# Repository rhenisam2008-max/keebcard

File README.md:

# KeebCard

A 3-key macropad keychain with an OLED display, built for Hack Club's Stardance event.

## Macropad Design

## Schematic

## PCB Layout

## Case (3D)

## Bill of Materials

| Part | Qty |
|---|---|
| Seeed XIAO RP2040 microcontroller | 1 |
| MX-style mechanical push switches | 3 |
| 0.91" 128×32 I2C OLED display | 1 |

## Firmware
Built with QMK. See `/Firmware` for source.

## Build folders
- `CAD/` — 3D printed case model
- `PCB/` — KiCad schematic and PCB design files
- `Firmware/` — QMK firmware source
- `production/` — Manufacturing-ready files (Gerbers, STEPs, compiled firmware)

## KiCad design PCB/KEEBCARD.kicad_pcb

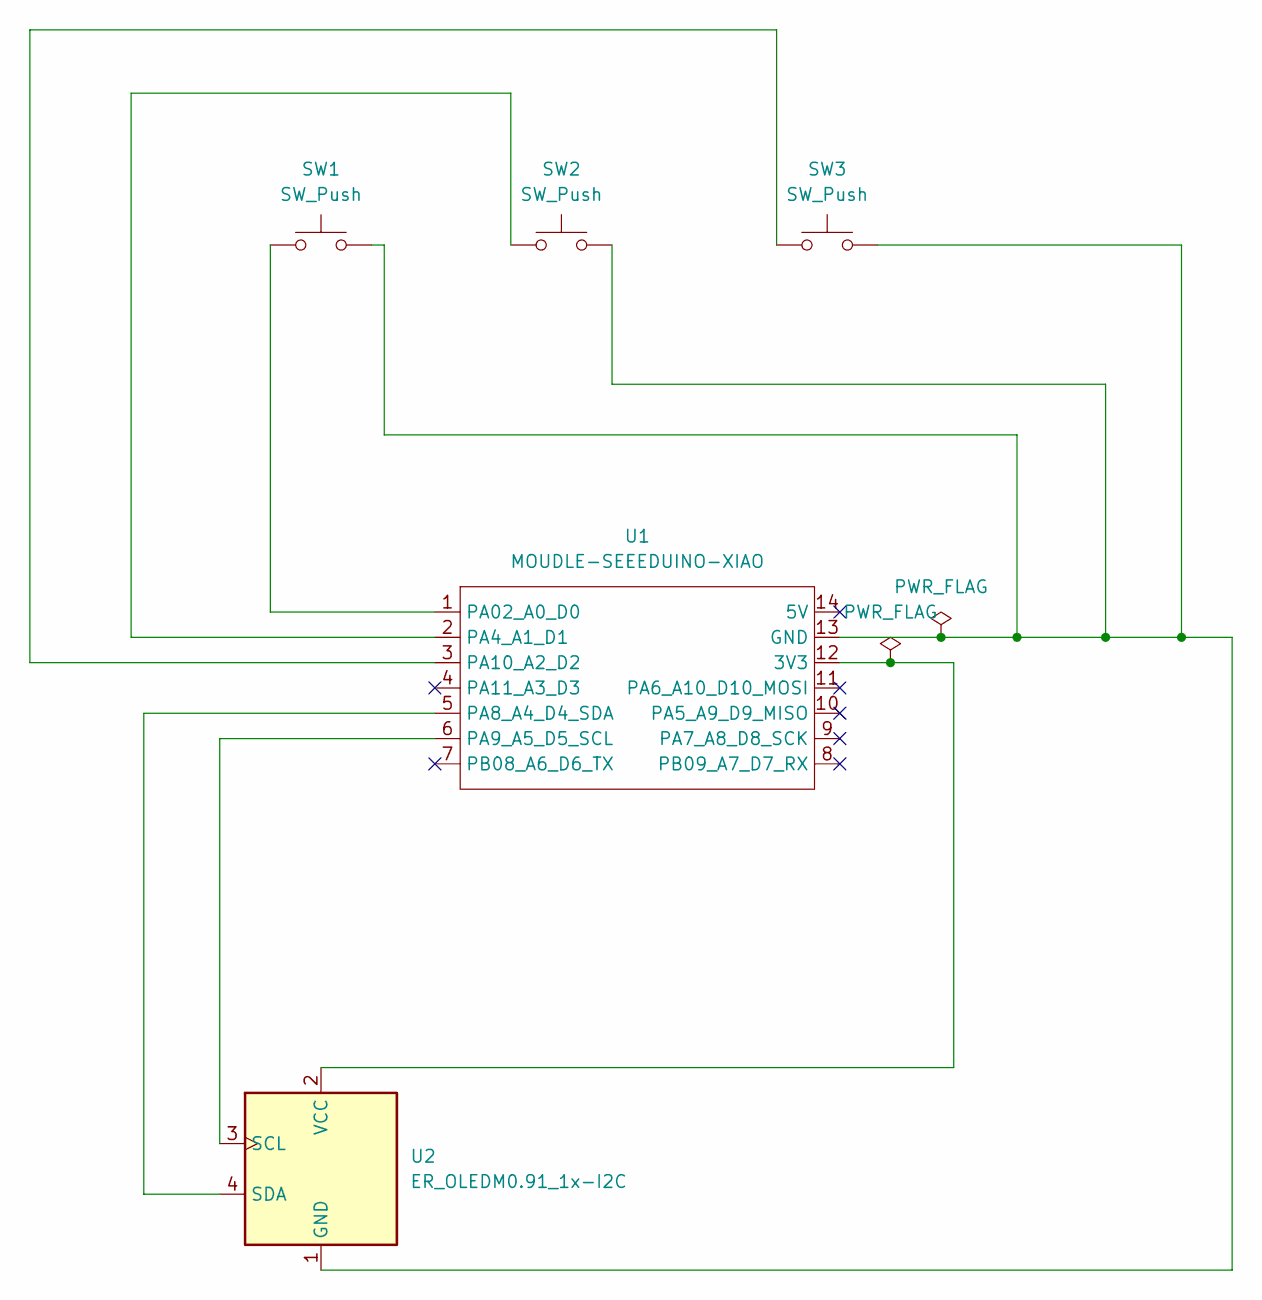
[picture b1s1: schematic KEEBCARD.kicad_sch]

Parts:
SW1, SW2, SW3: SW_Push; SW_Cherry_MX_1.00u_PCB
U1: MOUDLE-SEEEDUINO-XIAO; XIAO-Generic-Hybrid-14P-2.54-21X17.8MM
U2: ER_OLEDM0.91_1x-I2C

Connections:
unnamed: U1.12 (3V3), U2.2 (VCC)
unnamed: SW1.2, SW2.2, SW3.2, U1.13 (GND), U2.1 (GND)
unnamed: SW1.1, U1.1 (PA02_A0_D0)
unnamed: SW2.1, U1.2 (PA4_A1_D1)
unnamed: U1.5 (PA8_A4_D4_SDA), U2.4 (SDA)
unnamed: U1.6 (PA9_A5_D5_SCL), U2.3 (SCL)
unnamed: SW3.1, U1.3 (PA10_A2_D2)

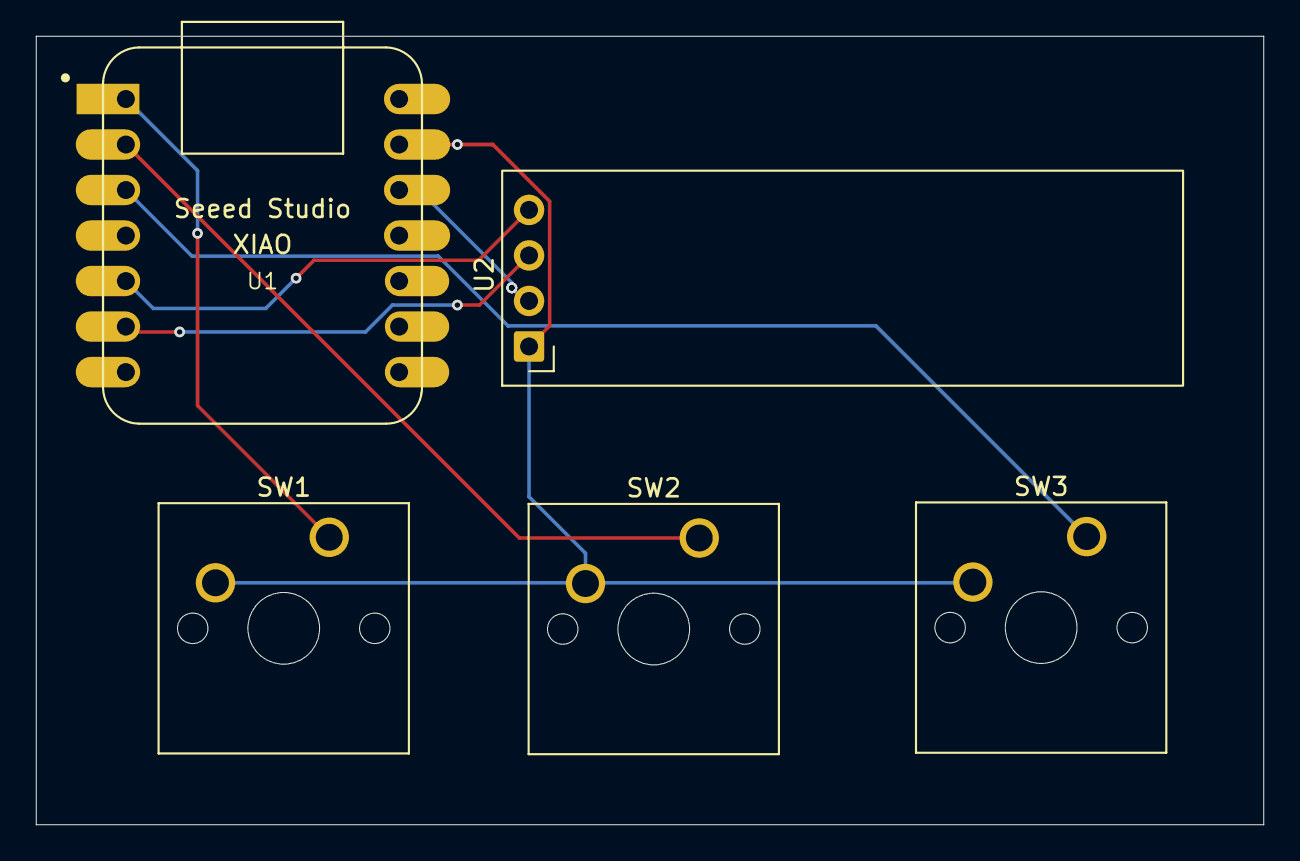
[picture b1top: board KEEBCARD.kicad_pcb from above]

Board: 2 copper layers, 68.5 x 44.0 mm, 5 parts (0 on the bottom side), 7 nets.

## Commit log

2026-06-26 Enhance README with project details and images
    Added detailed project description, images, and build folders.
2026-06-26 Fix image paths in README.md
    Updated image paths in the README to correct files.
2026-06-26 Fix image paths in README.md
    Updated image paths in README to include IMAGES directory.
